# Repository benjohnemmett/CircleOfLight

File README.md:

# CircleOfLight
Hardware &amp; firmware files for a simple PCB light game.

The hardware files are a PCB design which includes 12 LED lights in a circle and 3 push buttons. It is driven by an atmega328p.

The firmware is a multimode setup with a main menu and up to 12 programs. Currently only 3 programs are implemented: Reflex Game, Countdown Timer, and Hardware Test.

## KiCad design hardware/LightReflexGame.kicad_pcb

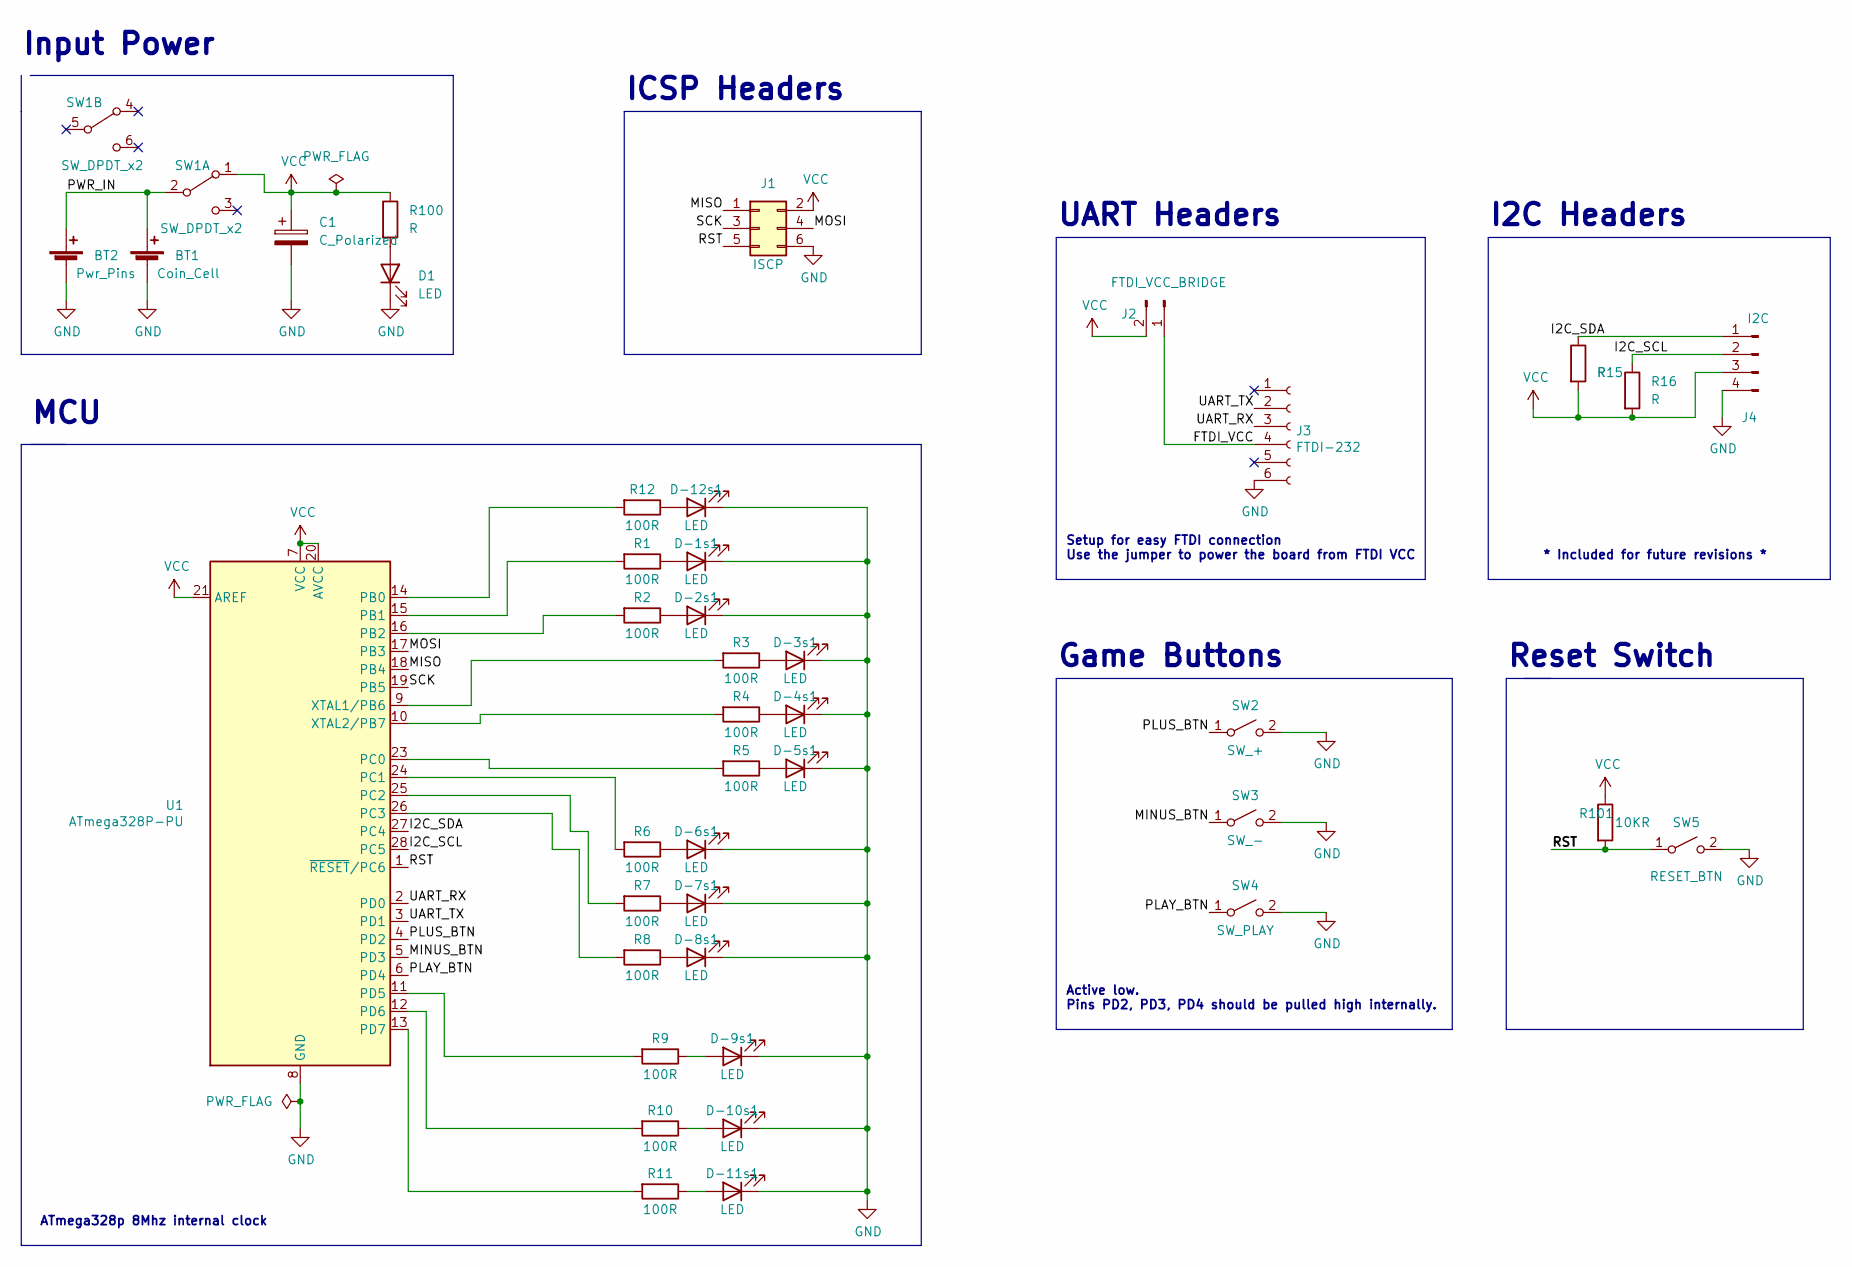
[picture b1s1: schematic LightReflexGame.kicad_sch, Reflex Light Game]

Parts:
BT1: Coin_Cell; BatteryHolder_bje_THT_1x2032
BT2: Pwr_Pins; PinHeader_1x02_P2.54mm_Vertical
C1: C_Polarized; CP_EIA-3528-12_Kemet-T
D1: LED; LED_0805_2012Metric
D-1s1, D-2s1, D-3s1, D-4s1, D-5s1, D-6s1, D-7s1, D-8s1, D-9s1, D-10s1, D-11s1, D-12s1: LED; LED_0805_2012Metric_Pad1.15x1.40mm_HandSolder
J1: ISCP; PinHeader_2x03_P2.54mm_Vertical
J2: FTDI_VCC_BRIDGE; PinHeader_1x02_P2.54mm_Vertical
J3: FTDI-232; PinHeader_1x06_P2.54mm_Vertical
J4: I2C; PinHeader_1x04_P2.54mm_Vertical
R1, R2, R3, R4, R5, R6, R7, R8, R9, R10, R11, R12: 100R; R_0805_2012Metric
R15, R16, R100: R; R_0805_2012Metric
R101: 10KR; R_0805_2012Metric
SW1: SW_DPDT_x2; SW_DPDT_MSS22D18_6pin_bje
SW2: SW_+; Switch_SPST_SMD_6mm_bje
SW3: SW_-; Switch_SPST_SMD_6mm_bje
SW4: SW_PLAY; Switch_SPST_SMD_6mm_bje
SW5: RESET_BTN; SW_SPST_FSMSM
U1: ATmega328P-PU; DIP-28_W7.62mm

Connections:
/FTDI_VCC: J2.1, J3.4
/I2C_SCL: J4.2, R16.1, U1.28 (PC5)
/I2C_SDA: J4.1, R15.1, U1.27 (PC4)
/MINUS_BTN: SW3.1 (A), U1.5 (PD3)
/MISO: J1.1, U1.18 (PB4)
/MOSI: J1.4, U1.17 (PB3)
/PLAY_BTN: SW4.1 (A), U1.6 (PD4)
/PLUS_BTN: SW2.1 (A), U1.4 (PD2)
/PWR_IN: BT1.1 (+), BT2.1 (+), SW1.2 (B); also elsewhere on the board
/RST: J1.5, R101.2, SW5.1 (A), U1.1 (~RESET/PC6)
/SCK: J1.3, U1.19 (PB5)
/UART_RX: J3.3, U1.2 (PD0)
/UART_TX: J3.2, U1.3 (PD1)
GND: BT1.2 (-), BT2.2 (-), C1.2, D1.1 (K), D-1s1.1 (K), D-2s1.1 (K), D-3s1.1 (K), D-4s1.1 (K), D-5s1.1 (K), D-6s1.1 (K), D-7s1.1 (K), D-8s1.1 (K), D-9s1.1 (K), D-10s1.1 (K), D-11s1.1 (K), D-12s1.1 (K), J1.6, J3.6, J4.4, SW2.2 (B), SW3.2 (B), SW4.2 (B), SW5.2 (B), U1.8 (GND), U1.22 (GND); also elsewhere on the board
unnamed: D1.2 (A), R100.2
unnamed: D-1s1.2 (A), R1.1
unnamed: D-2s1.2 (A), R2.1
unnamed: D-3s1.2 (A), R3.1
unnamed: D-4s1.2 (A), R4.1
unnamed: D-5s1.2 (A), R5.1
unnamed: D-6s1.2 (A), R6.1
unnamed: D-7s1.2 (A), R7.1
unnamed: D-8s1.2 (A), R8.1
unnamed: D-9s1.2 (A), R9.1
unnamed: D-10s1.2 (A), R10.1
unnamed: D-11s1.2 (A), R11.1
unnamed: D-12s1.2 (A), R12.1
unnamed: R1.2, U1.15 (PB1)
unnamed: R2.2, U1.16 (PB2)
unnamed: R3.2, U1.9 (XTAL1/PB6)
unnamed: R4.2, U1.10 (XTAL2/PB7)
unnamed: R5.2, U1.23 (PC0)
unnamed: R6.2, U1.24 (PC1)
unnamed: R7.2, U1.25 (PC2)
unnamed: R8.2, U1.26 (PC3)
unnamed: R9.2, U1.11 (PD5)
unnamed: R10.2, U1.12 (PD6)
unnamed: R11.2, U1.13 (PD7)
unnamed: R12.2, U1.14 (PB0)
VCC: C1.1, J1.2, J2.2, J4.3, R15.2, R16.2, R100.1, R101.1, SW1.1 (A), U1.7 (VCC), U1.20 (AVCC), U1.21 (AREF)

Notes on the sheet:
UART Headers
ICSP Headers
* Included for future revisions *
I2C Headers
ATmega328p 8Mhz internal clock
Reset Switch
Game Buttons
Setup for easy FTDI connection Use the jumper to power the board from FTDI VCC
MCU
Input Power
Active low. Pins PD2, PD3, PD4 should be pulled high internally.

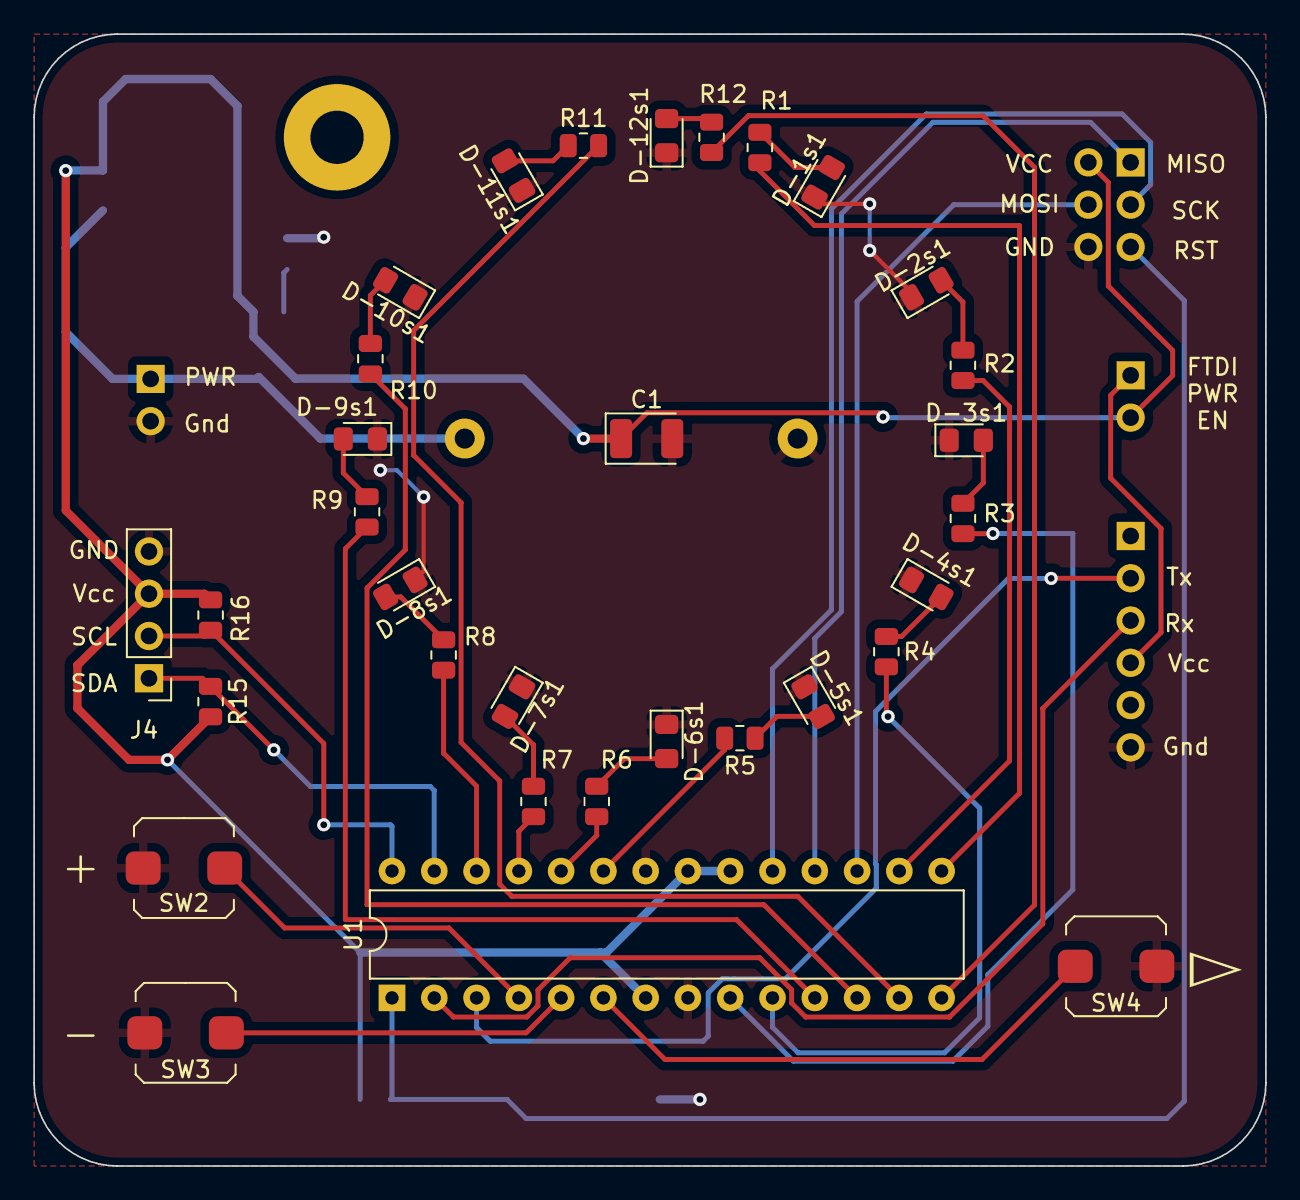
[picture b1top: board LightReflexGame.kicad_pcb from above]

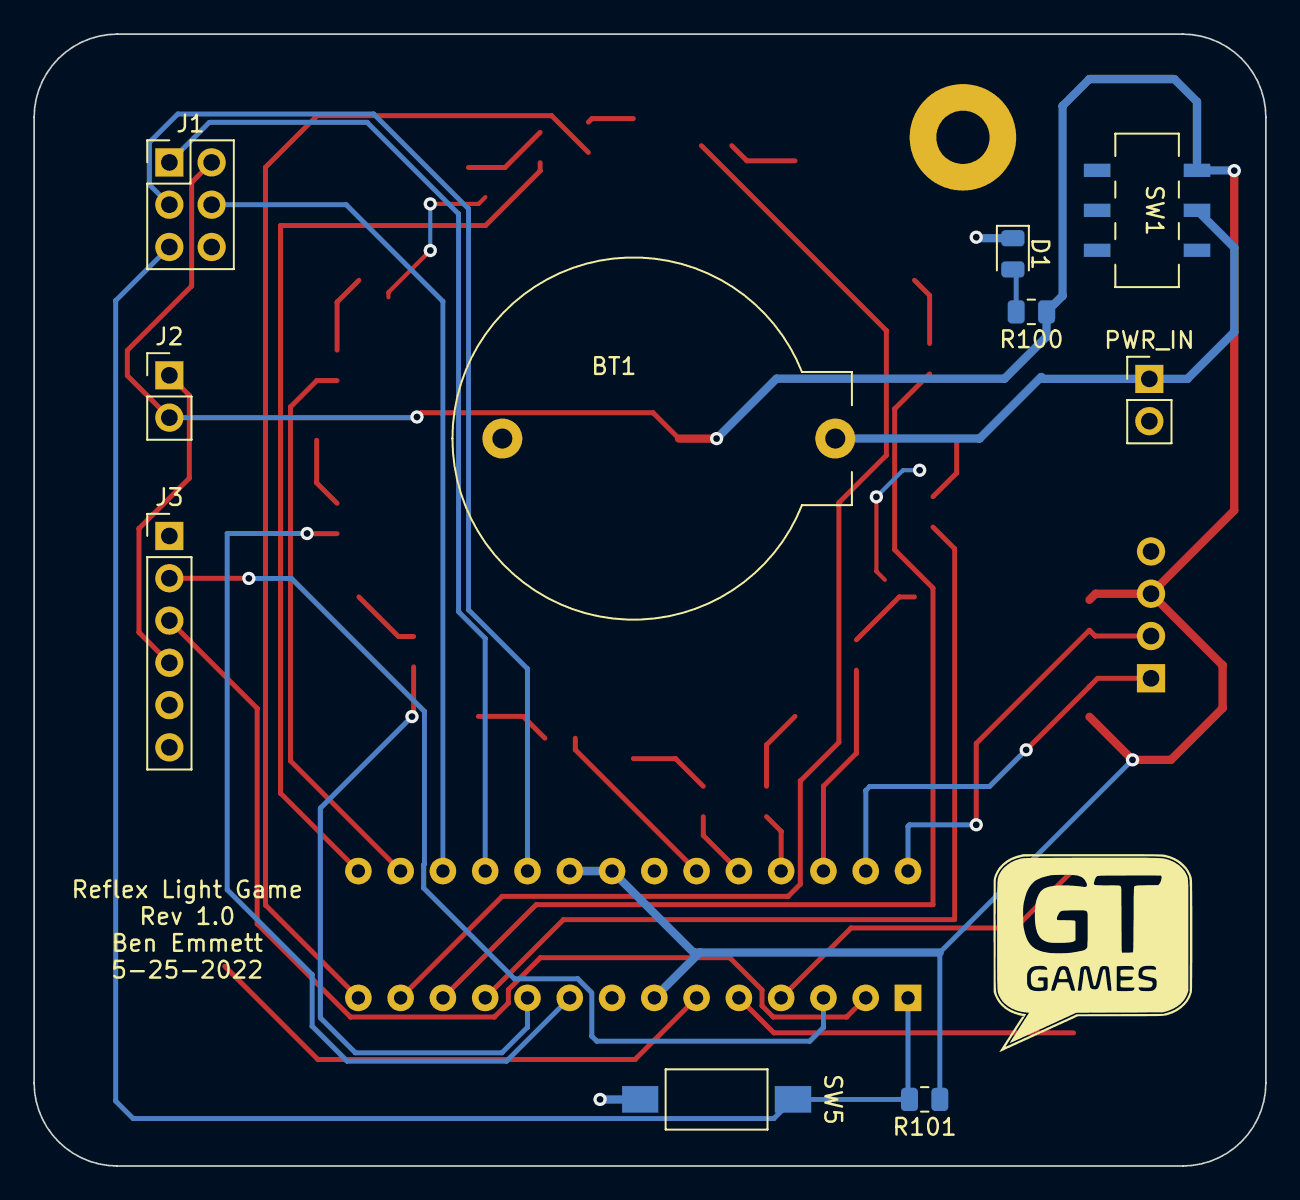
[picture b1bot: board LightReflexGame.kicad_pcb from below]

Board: 2 copper layers, 74.0 x 68.0 mm, 42 parts (10 on the bottom side), 40 nets.

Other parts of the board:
PWR_IN: Pwr_Pins; PinHeader_1x02_P2.54mm_Vertical

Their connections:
/PWR_IN: PWR_IN.1 (+); also elsewhere on the board
GND: PWR_IN.2 (-); also elsewhere on the board

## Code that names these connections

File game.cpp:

#include <avr/io.h>
#include <util/delay.h>
#include <avr/interrupt.h>
#include "uart.h"

#define LIGHT_01_PORT PORTB
#define LIGHT_02_PORT PORTB
#define LIGHT_03_PORT PORTB
#define LIGHT_04_PORT PORTB
#define LIGHT_05_PORT PORTC
#define LIGHT_06_PORT PORTC
#define LIGHT_07_PORT PORTC
#define LIGHT_08_PORT PORTC
#define LIGHT_09_PORT PORTD
#define LIGHT_10_PORT PORTD
#define LIGHT_11_PORT PORTD
#define LIGHT_12_PORT PORTB

#define LIGHT_01_DDR DDRB
#define LIGHT_02_DDR DDRB
#define LIGHT_03_DDR DDRB
#define LIGHT_04_DDR DDRB
#define LIGHT_05_DDR DDRC
#define LIGHT_06_DDR DDRC
#define LIGHT_07_DDR DDRC
#define LIGHT_08_DDR DDRC
#define LIGHT_09_DDR DDRD
#define LIGHT_10_DDR DDRD
#define LIGHT_11_DDR DDRD
#define LIGHT_12_DDR DDRB

#define LIGHT_01_PIN PB1
#define LIGHT_02_PIN PB2
#define LIGHT_03_PIN PB6
#define LIGHT_04_PIN PB7
#define LIGHT_05_PIN PC0
#define LIGHT_06_PIN PC1
#define LIGHT_07_PIN PC2
#define LIGHT_08_PIN PC3
#define LIGHT_09_PIN PD5
#define LIGHT_10_PIN PD6
#define LIGHT_11_PIN PD7
#define LIGHT_12_PIN PB0

#define BTN_DDR DDRD
#define BTN_PORT PORTD
#define BTN_PIN_REG PIND
#define PLAY_BTN_PIN PD4
#define MINUS_BTN_PIN PD3
#define PLUS_BTN_PIN PD2

volatile uint8_t activePin = 1;
uint8_t rotationIsClockWise = 0;
uint8_t currentCycle = 0;
uint8_t cyclesPerLight = 5;

typedef struct {
    uint8_t state;
    uint8_t transitionCounter;
    uint8_t isPressed;
} button_state_t;

button_state_t playButton = {0, 0, 0};
button_state_t plusButton = {0, 0, 0};
button_state_t minusButton = {0, 0, 0};

void SetOutputPins() {
    LIGHT_01_DDR |= _BV(LIGHT_01_PIN);
    LIGHT_02_DDR |= _BV(LIGHT_02_PIN);
    LIGHT_03_DDR |= _BV(LIGHT_03_PIN);
    LIGHT_04_DDR |= _BV(LIGHT_04_PIN);
    LIGHT_05_DDR |= _BV(LIGHT_05_PIN);
    LIGHT_06_DDR |= _BV(LIGHT_06_PIN);
    LIGHT_07_DDR |= _BV(LIGHT_07_PIN);
    LIGHT_08_DDR |= _BV(LIGHT_08_PIN);
    LIGHT_09_DDR |= _BV(LIGHT_09_PIN);
    LIGHT_10_DDR |= _BV(LIGHT_10_PIN);
    LIGHT_11_DDR |= _BV(LIGHT_11_PIN);
    LIGHT_12_DDR |= _BV(LIGHT_12_PIN);
}

void SetLightValue(uint8_t index, uint8_t value) {
    switch (index) {
        case 1:
            if (value) {LIGHT_01_PORT |= _BV(LIGHT_01_PIN);} else {LIGHT_01_PORT &= ~_BV(LIGHT_01_PIN);}
            break;
        case 2:
            if (value) {LIGHT_02_PORT |= _BV(LIGHT_02_PIN);} else {LIGHT_02_PORT &= ~_BV(LIGHT_02_PIN);}
            break;
        case 3:
            if (value) {LIGHT_03_PORT |= _BV(LIGHT_03_PIN);} else {LIGHT_03_PORT &= ~_BV(LIGHT_03_PIN);}
            break;
        case 4:
            if (value) {LIGHT_04_PORT |= _BV(LIGHT_04_PIN);} else {LIGHT_04_PORT &= ~_BV(LIGHT_04_PIN);}
            break;
        case 5:
            if (value) {LIGHT_05_PORT |= _BV(LIGHT_05_PIN);} else {LIGHT_05_PORT &= ~_BV(LIGHT_05_PIN);}
            break;
        case 6:
            if (value) {LIGHT_06_PORT |= _BV(LIGHT_06_PIN);} else {LIGHT_06_PORT &= ~_BV(LIGHT_06_PIN);}
            break;
        case 7:
            if (value) {LIGHT_07_PORT |= _BV(LIGHT_07_PIN);} else {LIGHT_07_PORT &= ~_BV(LIGHT_07_PIN);}
            break;
        case 8:
            if (value) {LIGHT_08_PORT |= _BV(LIGHT_08_PIN);} else {LIGHT_08_PORT &= ~_BV(LIGHT_08_PIN);}
            break;
        case 9:
            if (value) {LIGHT_09_PORT |= _BV(LIGHT_09_PIN);} else {LIGHT_09_PORT &= ~_BV(LIGHT_09_PIN);}
            break;
        case 10:
            if (value) {LIGHT_10_PORT |= _BV(LIGHT_10_PIN);} else {LIGHT_10_PORT &= ~_BV(LIGHT_10_PIN);}
            break;
        case 11:
            if (value) {LIGHT_11_PORT |= _BV(LIGHT_11_PIN);} else {LIGHT_11_PORT &= ~_BV(LIGHT_11_PIN);}
            break;
        case 12:
            if (value) {LIGHT_12_PORT |= _BV(LIGHT_12_PIN);} else {LIGHT_12_PORT &= ~_BV(LIGHT_12_PIN);}
            break;
    }
}

void SetupButtonPins() {
    BTN_DDR &= ~_BV(PLAY_BTN_PIN); // Make sure DDR is set to input (0)
    BTN_PORT |= _BV(PLAY_BTN_PIN); // Set internal pull up resister

    BTN_DDR &= ~_BV(PLUS_BTN_PIN); // Make sure DDR is set to input (0)
    BTN_PORT |= _BV(PLUS_BTN_PIN); // Set internal pull up resister

    BTN_DDR &= ~_BV(MINUS_BTN_PIN); // Make sure DDR is set to input (0)
    BTN_PORT |= _BV(MINUS_BTN_PIN); // Set internal pull up resister
}

void IncrementActiveLight() {
    activePin += 1;
    if (activePin > 12) {
        activePin = 1;
    }
}

void DecrementActiveLight() {
    if (activePin > 1) {
        activePin--;
    } else {
        activePin = 12;
    }
}

void UpdateButton(button_state_t *button, uint8_t isPressed) {
    if (button->state != isPressed) {
        button->transitionCounter++;

        if (button->transitionCounter >= 4) {
            button->state = isPressed;
            if (button->state != 0) {
                button->isPressed = 1;
            }
            button->transitionCounter = 0;
        }
    } else {
        button->transitionCounter = 0;
    }

}

void PollButtons() {
    uint8_t playButtonIsPressed = (BTN_PIN_REG & _BV(PLAY_BTN_PIN)) == 0;
    uint8_t plusButtonIsPressed = (BTN_PIN_REG & _BV(PLUS_BTN_PIN)) == 0;
    uint8_t minusButtonIsPressed = (BTN_PIN_REG & _BV(MINUS_BTN_PIN)) == 0;

    UpdateButton(&playButton, playButtonIsPressed);
    UpdateButton(&plusButton, plusButtonIsPressed);
    UpdateButton(&minusButton, minusButtonIsPressed);
}

int main() {
    SetupUart();
    EnableUartTransmission();
    SendStringToUart((char*)"Let the game begin!\r\n");

    SetOutputPins();
    SetupButtonPins();

    uint8_t pinToSet = activePin;

    while (1) {
        PollButtons();

        if (playButton.isPressed) {
            rotationIsClockWise = !rotationIsClockWise;
            playButton.isPressed = 0;
        }

        if (plusButton.isPressed) {
            if (cyclesPerLight > 0) {
                cyclesPerLight--;
            }
            plusButton.isPressed = 0;
        }

        if (minusButton.isPressed) {
            if (cyclesPerLight < 9) {
                cyclesPerLight++;
            }
            minusButton.isPressed = 0;
        }
        
        if (currentCycle >= cyclesPerLight) {
            if (rotationIsClockWise) {
                DecrementActiveLight();
            } else {
                IncrementActiveLight();
            }

            SetLightValue(pinToSet, 0);
            pinToSet = activePin;
            SetLightValue(pinToSet, 1);
            currentCycle = 0;
        }

        currentCycle++;
        _delay_ms(10);
    }
}

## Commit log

2022-06-02 Initial commit. Simple blink & uart test code implemented.
2022-06-16 Lights & buttons test working.
2022-06-16 changed game.cpp to main.cpp
2022-06-17 Restructerd code into separate classes LightController, ButtonManager, ReflexProgram. Functionally the same as before.
2022-06-19 Created Menu Program which hands control to other programs (only test program for now.
2022-06-19 Created test program class.
2022-06-19 Added support for button release delegate methods.
2022-06-21 ReflexProgram game mostly implemented. Lacking score display.
2022-06-21 Added score multiplier to Reflex game.
2022-06-21 Added force quit program with 2 sec minus button hold.
2022-06-23 ReflexProgram displays score after game. Started on CoundownTimer program.
2022-06-23 Created StateMachine template class
2022-07-18 Finished countdown timer program.
2022-07-18 Moved code to /firmware dir.
2022-07-19 Adding PCB files.
